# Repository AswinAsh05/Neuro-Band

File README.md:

# Neuro-Band

Neuro-Band is an ESP32-based wearable device designed for neural signal acquisition and monitoring.  
The system integrates motion sensing, wireless communication, and low-power design for portable bio-signal applications.

## Hardware Features
- ESP32-WROOM-32E microcontroller
- LiPo battery with TP4056 charging
- 3.3V regulation using ME6211 LDO
- MPU6050 motion sensor
- Electrode interface for neural signal acquisition
- Compact 2-layer PCB design

## Repository Structure
- **3D/** – 3D models of components
- **Files/** – KiCad schematic and PCB files
- **Gerber/** – Manufacturing files for PCB fabrication
- **Images/** – PCB renders and layout images

## License
This project is licensed under the MIT License.

## PCB Preview
### Top Layer

### 3D View

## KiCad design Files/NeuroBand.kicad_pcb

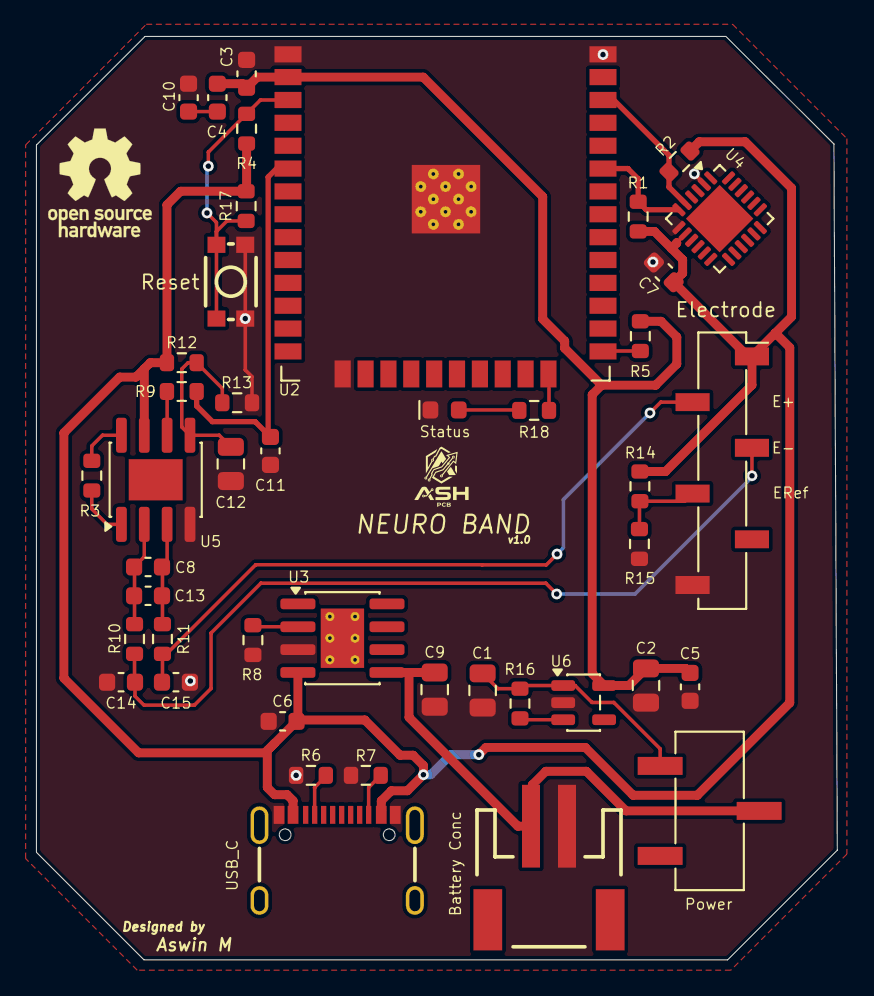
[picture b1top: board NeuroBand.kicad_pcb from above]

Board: 2 copper layers, 44.5 x 51.3 mm, 44 parts (0 on the bottom side), 26 nets.

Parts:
C1, C2, C9, C12: 10uF; C_0805_2012Metric
C3, C6: 1uF; C_0603_1608Metric
C4, C5, C7, C8, C10, C11: 0.1uF; C_0603_1608Metric
C13: 10nF; C_0603_1608Metric
C14, C15: 100pF; C_0603_1608Metric
D1: Red; LED_0603_1608Metric_Red
J1: Conn_01x06; 1x06_P2.54mm_Socket_Vertical_SMD_Pin1RightDown
J2: USB_C_Receptacle; USB-C_16
J3: JST_2mm_LiPo; JST_1x02_P2.0mm_Horizontal_SMD
Power: Switch_Slide_Top_CnK; Switch_Slide_Top_CnK_JS102011SCQN_8.5x3.5mm
R1, R2: 4.7k; R_0603_1608Metric
R3, R9, R18: 1k; R_0603_1608Metric
R4, R5, R12, R13, R16, R17: 10k; R_0603_1608Metric
R6, R7: 5.1k; R_0603_1608Metric
R8: 2k; R_0603_1608Metric
R10, R11: 100k; R_0603_1608Metric
R14, R15: 1m; R_0603_1608Metric
SW1: SMD_4.6x2.8mm_h1.9mm; Push_SMD_4.6x2.8mm_h1.9mm
U2: ESP32-WROOM-32E; ESP32-WROOM-32D
U3: TP4056-42-ESOP8; SOIC-8-1EP_3.9x4.9mm_P1.27mm_EP2.41x3.3mm_ThermalVias
U4: MPU6050; QFN-24-1EP_4x4mm_P0.5mm_EP2.65x2.65mm
U5: AD620; SOIC-8-1EP_3.9x4.9mm_P1.27mm_EP2.29x3mm
U6: ME6211C33M5; SOT-23-5

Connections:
+3.3V: C6.2 (-), C7.2 (-), J1.1, J2.VBUS, R1.1 (+), R2.2 (-), R4.2 (-), R12.1 (+), R14.1 (+), R17.1 (+), U3.4 (V_{CC}), U4.8 (VCC), U5.7 (Vs+)
ADC: C11.2 (-), R9.2 (-), U2.6 (IO34)
Battery+: C9.2 (-), J3.2 (+), Power.2 (B), U3.5 (BAT)
EN: R4.1 (+), R17.2 (-), SW1.1, U2.3 (EN)
Electrode Ref: J1.4, R14.2 (-), R15.1 (+)
Electrode+: C15.2 (-), J1.2, R11.1 (+)
Electrode-: C14.2 (-), J1.3, R10.1 (+)
GND: C1.2 (-), C2.2 (-), C3.2 (-), C5.2 (-), C6.1 (+), C7.1 (+), C9.1 (+), C10.2 (-), C11.1 (+), C12.1 (+), C14.1 (+), C15.1 (+), D1.1 (K), J1.6, J2.GND, J3.1 (-), R6.2 (-), R7.2 (-), R8.2 (-), R13.2 (-), R15.2 (-), SW1.2, U2.1 (GND), U2.15 (GND), U2.38 (GND), U2.39 (GND), U3.3 (GND), U4.2 (ADO), U4.7 (GND), U5.4 (Vs-), U6.2 (V_{SS})
unnamed: C1.1 (+), Power.1 (A), R16.2 (-), U6.1 (V_{IN})
unnamed: C4.2 (-), C10.1 (+)
unnamed: C8.1 (+), C13.1 (+), R11.2 (-), U5.3 (+)
unnamed: C8.2 (-), C13.2 (-), R10.2 (-), U5.2 (-)
unnamed: D1.2 (A), R18.2 (-)
unnamed: J2.A5 (CC1), R6.1 (+)
unnamed: J2.B5 (CC2), R7.1 (+)
unnamed: R3.1 (+), U5.8 (Rg)
unnamed: R3.2 (-), U5.1 (Rg)
unnamed: R5.2 (-), U2.25 (IO0)
unnamed: R8.1 (+), U3.2 (PROG)
unnamed: R9.1 (+), U5.6
unnamed: R16.1 (+), U6.3 (CE)
unnamed: R18.1 (+), U2.24 (IO2)
Ref: C12.2 (-), R12.2 (-), R13.1 (+), U5.5 (Ref)
SCL: R2.1 (+), U2.36 (IO22), U4.5 (SDA)
SDA: R1.2 (-), U2.33 (IO21), U4.6 (SCL)
VDD: C2.1 (+), C3.1 (+), C4.1 (+), C5.1 (+), R5.1 (+), U2.2 (VDD), U6.5 (V_{OUT})

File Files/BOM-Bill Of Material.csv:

"Reference","Qty","Value","DNP","Exclude from BOM","Exclude from Board","Footprint","Datasheet"
"C1,C2,C9,C12","4","10uF","","","","Capacitor_SMD:C_0805_2012Metric",""
"C3,C6","2","1uF","","","","Capacitor_SMD:C_0603_1608Metric",""
"C4,C5,C7,C8,C10,C11","6","0.1uF","","","","Capacitor_SMD:C_0603_1608Metric",""
"C13","1","10nF","","","","Capacitor_SMD:C_0603_1608Metric",""
"C14,C15","2","100pF","","","","Capacitor_SMD:C_0603_1608Metric",""
"D1","1","Red","","","","PCM_SparkFun-LED:LED_0603_1608Metric_Red","https://www.kingbrightusa.com/images/catalog/SPEC/APT1608SURCK.pdf"
"J1","1","Conn_01x06","","","","PCM_SparkFun-Connector:1x06_P2.54mm_Socket_Vertical_SMD_Pin1RightDown","https://gct.co/files/drawings/bg125.pdf"
"J2","1","USB_C_Receptacle","","","","PCM_SparkFun-Connector:USB-C_16","https://www.usb.org/sites/default/files/documents/usb_type-c.zip"
"J3","1","JST_2mm_LiPo","","","","PCM_SparkFun-Connector:JST_1x02_P2.0mm_Horizontal_SMD","~"
"R1,R2","2","4.7k","","","","Resistor_SMD:R_0603_1608Metric",""
"R3,R9,R18","3","1k","","","","Resistor_SMD:R_0603_1608Metric",""
"R4,R5,R12,R13,R16,R17","6","10k","","","","Resistor_SMD:R_0603_1608Metric",""
"R6,R7","2","5.1k","","","","Resistor_SMD:R_0603_1608Metric",""
"R8","1","2k","","","","Resistor_SMD:R_0603_1608Metric",""
"R10,R11","2","100k","","","","Resistor_SMD:R_0603_1608Metric",""
"R14,R15","2","1m","","","","Resistor_SMD:R_0603_1608Metric",""
"SW1","1","SMD_4.6x2.8mm_h1.9mm","","","","PCM_SparkFun-Switch:Push_SMD_4.6x2.8mm_h1.9mm","https://www.ckswitches.com/media/1479/kmr2.pdf"
"SW2","1","Switch_Slide_Top_CnK","","","","PCM_fab:Switch_Slide_Top_CnK_JS102011SCQN_8.5x3.5mm","https://www.ckswitches.com/media/1422/js.pdf"
"U2","1","ESP32-WROOM-32E","","","","RF_Module:ESP32-WROOM-32D","https://www.espressif.com/sites/default/files/documentation/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"
"U3","1","TP4056-42-ESOP8","","","","Package_SO:SOIC-8-1EP_3.9x4.9mm_P1.27mm_EP2.41x3.3mm_ThermalVias","https://www.lcsc.com/datasheet/lcsc_datasheet_2410121619_TOP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"
"U4","1","MPU6050","","","","Package_DFN_QFN:QFN-24-1EP_4x4mm_P0.5mm_EP2.65x2.65mm",""
"U5","1","AD620","","","","Package_SO:SOIC-8-1EP_3.9x4.9mm_P1.27mm_EP2.29x3mm","https://www.analog.com/media/en/technical-documentation/data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"
"U6","1","ME6211C33M5","","","","Package_TO_SOT_SMD:SOT-23-5","https://www.lcsc.com/datasheet/lcsc_datasheet_2304140030_MIC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"

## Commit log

2026-03-10 Create LICENSE
2026-03-10 Add 3D view section and image to README
